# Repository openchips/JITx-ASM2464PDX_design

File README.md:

** Introduction
This is a project showing of the high speed routing capabilities within JITx. It is currently a work in progress towards an open source USB4/TBT4 to between 1 and 4 M.2 PCIe connectors based on the AsMedia ASM2464PDX chip.

The software used to write this complex design is JITx, a new and amazing code based EDA. Check out [JITx plans and **their free for open source license**.](https://hubs.la/Q02-p5-70)
Feel free to reach out to me or to their support on Discord to learn more, or plan a demo session to see how the future of PCB desgn will look like.

** To-do
WIP

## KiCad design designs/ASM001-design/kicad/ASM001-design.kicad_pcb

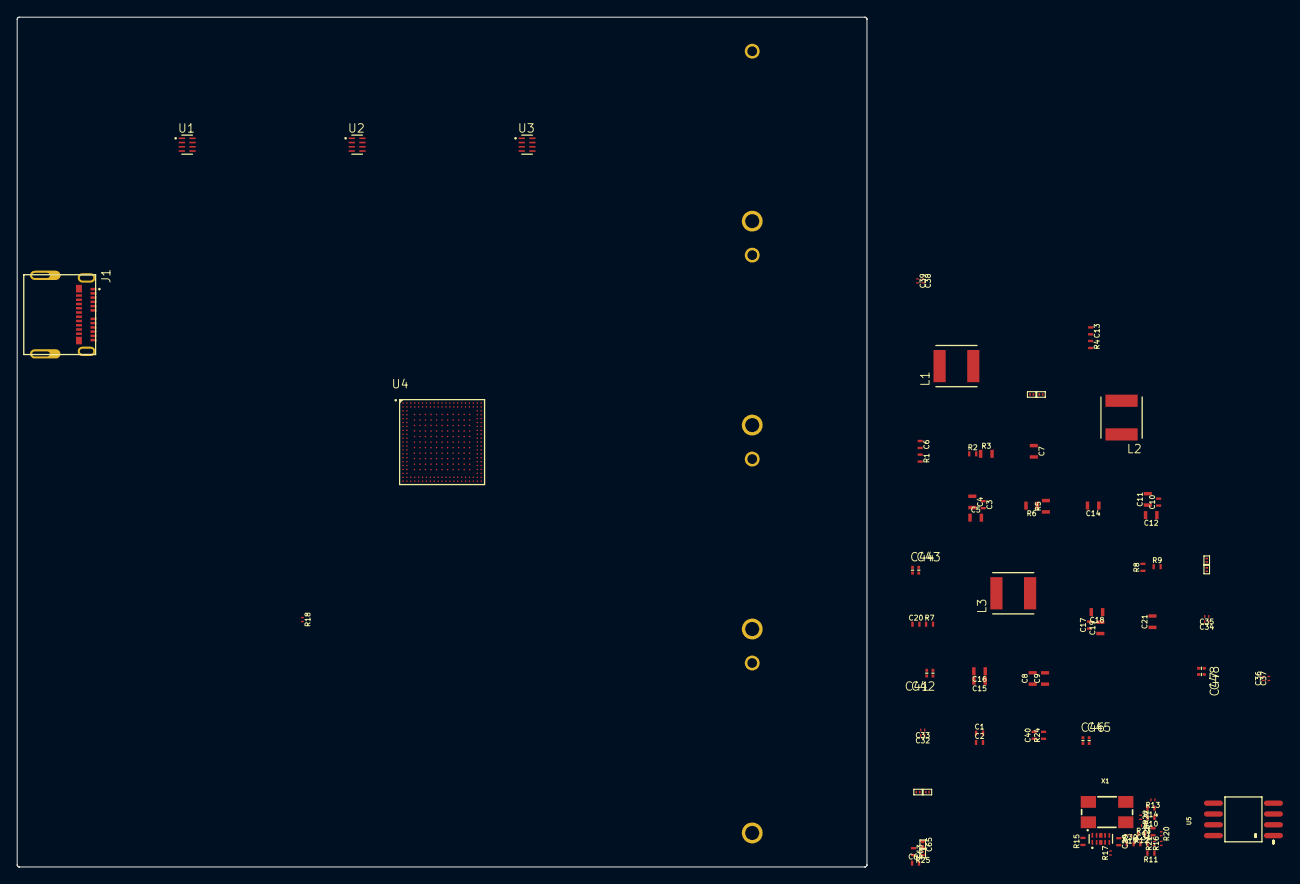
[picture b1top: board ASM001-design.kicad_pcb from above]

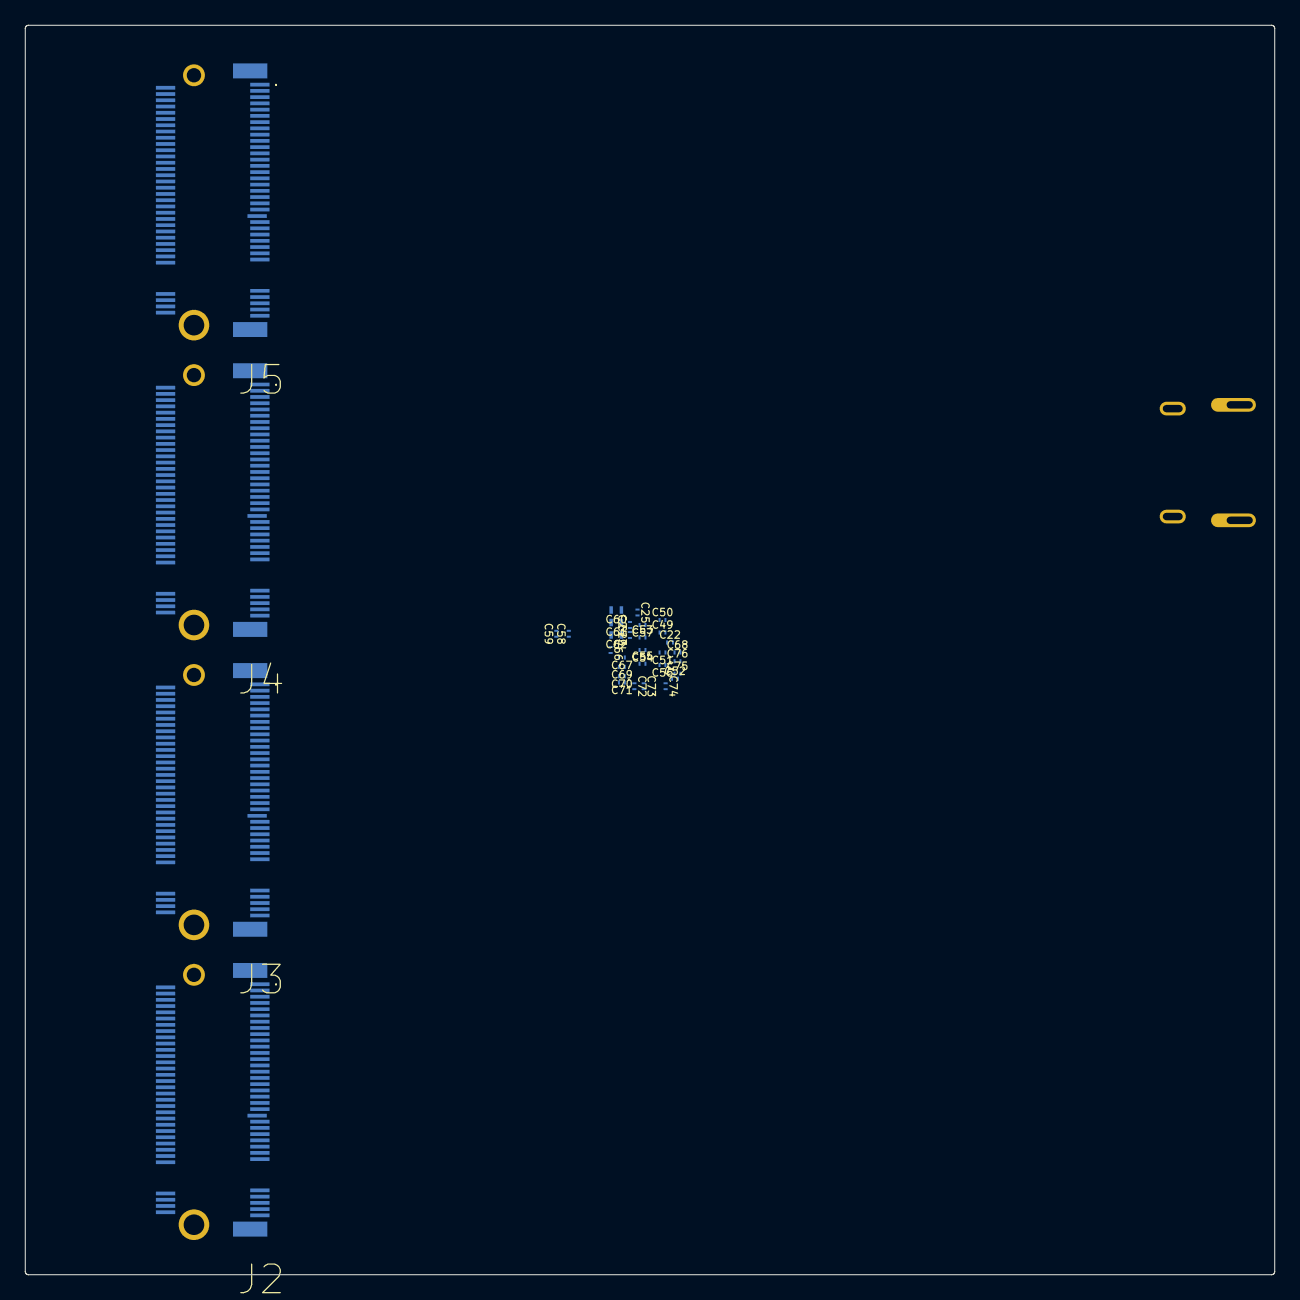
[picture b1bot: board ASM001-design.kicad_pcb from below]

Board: 6 copper layers, 100.0 x 100.0 mm, 122 parts (33 on the bottom side), 107 nets, no tracks yet.

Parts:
C1, C2: 820n; Pkg0402_12
C3: 4.7n; Pkg0402_5
C4, C5: 10u; Pkg0603_5
C6: 100n; Pkg0402_15
C7: 10p; Pkg0603_8
C8, C9: 390n; Pkg0603_10
C10: 4.7n; Pkg0402_3
C11, C12: 10u; Pkg0603_4
C13: 100n; Pkg0402_14
C14: 10p; Pkg0603_7
C15, C16: 3.3u; Pkg0603_9
C17: 4.7n; Pkg0402_2
C18, C19: 10u; Pkg0603_3
C20: 100n; Pkg0402_13
C21: 10p; Pkg0603_6
C22, C23, C24, C25: 220n; Pkg0201
C28: 10p; LP_3
C29: 1u; Pkg0402_6
C30, C31: 2.2n; Pkg0402_8
C32, C33, C36, C37: 220n; Pkg0201_5
C34, C35, C38, C39: 470n; Pkg0201_1
C40: 4.7n; Pkg0402_11
C41, C42, C43, C44, C45, C46, C47, C48: 220n; SMT_0201
C49, C50, C51, C52, C53, C54, C55, C56, C57, C58, C59: 2.2u; Pkg0201_4
C60, C61, C62: 10u; Pkg0402_20
C63, C64, C65: 10u; Pkg0402_10
C66, C67, C68, C69, C70, C71, C72, C73, C74, C75, C76: 2.2u; Pkg0201_7
J1: 2012670005; USB_TYPE_C_CONNECTOR
J2, J3, J4, J5: 1-2199230-6; Pkg_121992306
L1, L2, L3: 1.5u; MOLDED
R1: 0R; Pkg0402_19
R2: 3K09; Pkg0402_1
R3: 7K5; Pkg0603_2
R4: 0R; Pkg0402_18
R5: 10K; Pkg0603
R6: 7K32; Pkg0603_1
R7: 0R; Pkg0402_17
R8: 24K; Pkg0402
R9: 7K68; Pkg0402_4
R10, R11, R12, R15: 4K7; Pkg0402_16
R13: 100K; Pkg0201_2
R14: 12K1; Pkg0402_9
R16, R17, R18, R19, R20, R21, R22, R23: 200K; Pkg0201_6
R24: 0R; Pkg0402_7
R25: 0R; Pkg0201_3
U1, U2, U3: TPS62932DRL; SOT50P160_8N
U4: ASM2464PDX; BGA273N46P21X21_1000X1000X98
U5: W25Q32JVSSIQ; LP_1
U6: ESD224DQAR; USON_10
U7, U8, U9, U10, U11, U12, U13, U14: ESD132-B1-W0201 E6327; LP_2
X1: ABMM2-25.000MHZ-D1-T; LP

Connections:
BST: C6.1, U1.6
FB: C21.2, R8.2, R9.1, U3.8
GND: C22.2, C23.2, C24.2, C25.2, C29.2, C30.2, C31.2, C40.2, C49.2, C50.2, C51.2, C52.2, C53.2, C54.2, C55.2, C56.2, C57.2, C58.2, C59.2, C60.2, C61.2, C62.2, C63.2, C64.2, C65.2, C66.2, C67.2, C68.2, C69.2, C70.2, C71.2, C72.2, C73.2, C74.2, C75.2, C76.2, J1.A1, J1.A12, J1.B1, J1.B12, J2.3, J2.9, J2.15, J2.33, J2.39, J2.45, J2.51, J2.57, J2.71, J2.73, J3.3, J3.9, J3.15, J3.33, J3.39, J3.45, J3.51, J3.57, J3.71, J3.73, J4.3, J4.9, J4.15, J4.33, J4.39, J4.45, J4.51, J4.57, J4.71, J4.73, J5.3, J5.9, J5.15, J5.33, J5.39, J5.45, J5.51, J5.57, J5.71, J5.73, R14.2, R15.2, R16.2, R17.2, R18.2, R19.2, R20.2, R21.2, R22.2, R23.2, R24.2, U4.AA1, U4.AA2, U4.AA5, U4.AA9, U4.AA12, U4.AA14, U4.AA16, U4.AA18, U4.AA20, U4.AA21, U4.D4, U4.D5, U4.D11, U4.D17, U4.D18, U4.E4, U4.E5, U4.E17, U4.E18, U4.F4, U4.F5, U4.F8, U4.F17, U4.F18, U4.H4, U4.H8, U4.H17, U4.H18, U4.J4, U4.J5, U4.J6, U4.J11, U4.K2, U4.L1, U4.L2, U4.L4, U4.L5, U4.L9, U4.L13, U4.M20, U4.M21, U4.N1, U4.N2, U4.N4, U4.N5, U4.N9, U4.N11, U4.N13, U4.N17, U4.N18, U4.P4, U4.P5, U4.P9, U4.P11, U4.P17, U4.P18, U4.P20, U4.P21, U4.R1, U4.R2, U4.T4, U4.T5, U4.T17, U4.T18, U4.T20, U4.T21, U4.U1, U4.U2, U4.U4, U4.U5, U4.U17, U4.U18, U4.V4, U4.V5, U4.V6, U4.V8, U4.V9, U4.V11, U4.V13, U4.V14, U4.V16, U4.V17, U4.V18, U4.V20, U4.V21, U4.W1, U4.W2, U4.Y3, U4.Y5, U4.Y9, U4.Y12, U4.Y14, U4.Y16, U4.Y18, U4.Y20, U4.Y21, U5.4, U6.3, U6.8, X1.2, X1.4
GND1: C1.2, C2.2, C3.2, C4.2, C5.2, C8.2, C9.2, C10.2, C11.2, C12.2, C15.2, C16.2, C17.2, C18.2, C19.2, R3.2, R6.2, R9.2, U1.4, U2.4, U3.4
IC_SW_BST: C20.1, U3.6
IC_SW_FB: C14.2, R5.2, R6.1, U2.8
P1V9: C10.1, C11.1, C12.1, C14.1, C63.1, C64.1, C65.1, C66.1, C67.1, C68.1, C69.1, C70.1, C71.1, C72.1, C73.1, C74.1, C75.1, C76.1, L2.2, R5.1, U4.L6, U4.L16, U4.L17, U4.L18, U4.L20, U4.L21, U4.N6, U4.N16, U4.P6, U4.P16, U4.T6, U4.T16, U4.U6, U4.U11, U4.U13, U4.U14, U4.U16
P1V13: C3.1, C4.1, C5.1, C7.1, C22.1, C23.1, C24.1, C25.1, C49.1, C50.1, C51.1, C52.1, C53.1, C54.1, C55.1, C56.1, C57.1, C58.1, C59.1, C60.1, C61.1, C62.1, L1.2, R2.1, U4.D14, U4.D16, U4.E11, U4.E14, U4.E16, U4.F9, U4.F11, U4.F14, U4.F16, U4.H9, U4.H11, U4.H13, U4.H14, U4.H16, U4.J8, U4.J9, U4.J13, U4.J14, U4.J16, U4.J17, U4.J18, U4.J20, U4.J21, U4.K20, U4.K21, U4.L8, U4.L11, U4.L14, U4.N8, U4.N14, U4.P8, U4.P13, U4.P14, U4.T8, U4.T9, U4.T11, U4.T13, U4.T14, U4.U8, U4.U9
P3V3: C17.1, C18.1, C19.1, C21.1, L3.2, R8.1, R10.2, R11.2, R12.2, R13.2, R25.1, U4.D6, U4.D8, U4.D9, U4.D13, U4.E6, U4.E8, U4.E9, U4.E13, U4.F6, U4.F13, U4.H6, U5.8
RST#: C29.1, R13.1, U4.H1
R_p1: C40.1, J1.M1, J1.M2, J1.M3, J1.M4, R24.1
SHIELD: J4.MP1, J4.MP2
SHIELD1: J5.MP1, J5.MP2
SHIELD2: J2.MP1, J2.MP2
SHIELD3: J3.MP1, J3.MP2
SPI_CLK: U4.A5, U5.6
SPI_CS#: U4.A2, U5.1
SPI_DI: U4.A4, U5.5
SPI_DO: U4.A3, U5.2
SPI_IO2: R10.1, U5.3
SPI_IO3: R11.1, U5.7
SW-NODE: L1.1, R1.2, U1.5
SW-NODE1: L3.1, R7.2, U3.5
SW-NODE2: L2.1, R4.2, U2.5
SW_BST: C13.1, U2.6
SW_FB: C7.2, R2.2, R3.1, U1.8
TEST_EN: R15.1, U4.H21
UART_TX: R12.1, U4.B21
UREXT: R14.1, U4.AA3
VBUS: J1.A4, J1.A9, J1.B4, J1.B9, U4.G1
VBUS1: C1.1, C2.1, C8.1, C9.1, C15.1, C16.1, U1.3, U2.3, U3.3
VCCA33: R25.2, U4.H5
V_3V3: J5.2, J5.4, J5.12, J5.14, J5.16, J5.18, J5.70, J5.72, J5.74
V_3V3_1: J4.2, J4.4, J4.12, J4.14, J4.16, J4.18, J4.70, J4.72, J4.74
V_3V3_2: J2.2, J2.4, J2.12, J2.14, J2.16, J2.18, J2.70, J2.72, J2.74
V_3V3_3: J3.2, J3.4, J3.12, J3.14, J3.16, J3.18, J3.70, J3.72, J3.74
XI: C28.1, U4.AA4, X1.1
XO: C28.2, U4.Y4, X1.3
asm2464pdx_usb-c_cc0: C30.1, J1.A5, U4.AA6
asm2464pdx_usb-c_cc1: C31.1, J1.B5, U4.Y6
asm2464pdx_usb-c_sbu0: J1.A8, U4.K1
asm2464pdx_usb-c_sbu1: J1.B8, U4.J1
dst-ep_control_CLKREQ#: J4.52, U4.A19
dst-ep_control_CLKREQ#1: J2.52, U4.A20
dst-ep_control_CLKREQ#2: J3.52, U4.A14
dst-ep_control_PERST#: J3.50, U4.E21
dst-ep_control_PERST#1: J4.50, U4.G21
dst-ep_control_PERST#2: J5.50, U4.D21
dst-ep_control_PEWAKE#: J5.54, U4.A9
dst-ep_control_PEWAKE#1: J4.54, U4.A13
dst-ep_control_PEWAKE#2: J2.54, U4.A12
dst-ep_control_PEWAKE#3: J3.54, U4.A11
dst-ep_data_lane0_RX_P: J2.43, U4.W21
dst-ep_data_refclk_N: J5.53, U4.Y7
dst-ep_data_refclk_N1: J4.53, U4.Y8
dst-ep_data_refclk_N2: J2.53, U4.Y11
dst-ep_data_refclk_P: J5.55, U4.AA7
dst-ep_data_refclk_P1: J2.55, U4.AA11
dst-ep_data_refclk_P2: J3.55, U4.AA10
elem_elem_p1: C13.2, R4.1
elem_p1: C6.2, R1.1
elem_p2: C20.2, R7.1
esd-pair_A_P: J1.A6, J1.B6, U4.M1, U6.5, U6.6
esd-pair_B_N: J1.A7, J1.B7, U4.M2, U6.4, U6.7
src-ep_control_CLKREQ#: J5.52, U4.A15
src-ep_control_PERST#: J2.50, U4.F21
src-ep_data_lane0_RX_N: J5.41, U4.Y13
src-ep_data_lane0_RX_N1: J2.41, U4.W20
src-ep_data_lane0_RX_N2: J3.41, U4.AA19
src-ep_data_lane0_RX_N3: J4.41, U4.N20
src-ep_data_lane0_RX_P: J4.43, U4.N21
src-ep_data_lane0_RX_P1: J5.43, U4.AA13
src-ep_data_lane0_RX_P2: J3.43, U4.Y19
src-ep_data_refclk_N: J3.53, U4.Y10
src-ep_data_refclk_P: J4.55, U4.AA8
x_A_N: C35.2, U10.2
x_A_N1: C37.2, U12.2
x_A_N2: C42.2, U4.U21
x_A_N3: C48.1, U4.AA15
x_A_N4: C37.1, J1.B3, R23.1, U4.V1, U12.1
x_A_N5: C46.1, U4.R21
x_A_N6: C39.2, U14.1
x_A_N7: C39.1, J1.A10, R21.1, U4.Y1, U14.2
x_A_N8: C44.2, U4.AA17
x_A_P: C43.2, U4.Y17
x_A_P1: C38.1, J1.A11, R20.1, U4.Y2, U13.2
x_A_P2: C32.1, U7.2
x_A_P3: C34.2, U9.2
x_A_P4: C36.2, U11.2
x_A_P5: C41.2, U4.U20
x_A_P6: C47.1, U4.Y15
x_A_P7: C34.1, J1.B11, R16.1, U4.P1, U9.1
x_A_P8: C45.1, U4.R20
x_A_P9: C38.2, U13.1
x_B_N: C44.1, J3.47
x_B_N1: C33.1, U8.2
x_B_N2: C48.2, J5.47
x_B_N3: C46.2, J4.47
x_B_N4: C35.1, J1.B10, R17.1, U4.P2, U10.1
x_B_N5: C42.1, J2.47
x_B_N6: C33.2, J1.A3, R19.1, U4.T2, U8.1
x_B_P: C32.2, J1.A2, R18.1, U4.T1, U7.1
x_B_P1: C43.1, J3.49
x_B_P2: C47.2, J5.49
x_B_P3: C45.2, J4.49
x_B_P4: C36.1, J1.B2, R22.1, U4.V2, U11.1
x_B_P5: C41.1, J2.49

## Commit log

2024-11-19 Initialcommit
    Current state of the work in progress on this project
2024-11-19 Cleanup
2024-11-19 Updated ASM2464PDX component to more modern JSL syntax. jitx.exe crashes with unknown code
2024-11-19 Update files
2024-12-07 Update device definitions and some tests
2024-12-08 Update USB4 supports, WIP
2024-12-10 Attempt to add usb-c support to the USB4 connector
2024-12-11 Updated USB4 connector to finally render
2024-12-11 Add .viw to gitignore
2024-12-11 Add PCIe constraints and iterate over the 2 USB channels. TODO: strange error about unroutable pin
2024-12-11 Cleaner way of iterating over USB-C lanes
2024-12-12 Semi-working, rendering at least
2024-12-12 Bard files
2024-12-16 Updates to the USB4 connector
    Thanks @callendorph for your feedback and help, it has been super valuable.
2025-01-11 Properly name and version the project. Small changes to update to latest jsl
2025-01-11 Fill in some details from the USB4 cable and system guide
2025-01-11 Some toying around to see if I can figure out why it's not connected up internally
2025-01-11 require usb-data : dual-pair from self
2025-01-11 Trial and error
2025-01-11 Add generic Molex USB-C and try to connect up the USB4 constraints using the usb-c support
    It renders, but it doesn't connect up properly due to components\Generic\USBTypeC.stanza:277
2025-01-11 Add in the lane-pair suppport by Carl, maybe useful?
2025-01-11 Add 'require usb_c_inst:usb_c from self' to force error sooner.
2025-01-12 Changed to a flat component with all the constraints in the main design
2025-01-14 Some cleanup, added power supplies, starting to hook up components
2025-01-14 Large update to design, started to split components into separate pcb-modules
2025-01-14 Change PCIE-V3 back to PCIE-V4
2025-01-15 More big updates
2025-01-16 More design updates according to reference design.
2025-01-17 Start placement in code
2025-01-18 Add GND and VDD planes
2025-01-19 Cleaned up power supplies. Has issues with the PCIe 4x1 require
2025-01-19 Random testing
2025-01-20 Small bugfixes as per review by @bhusang
2025-01-22 WIP adding decoupling caps and some small changes
2025-01-24 Sloppy mix of older than jsl update esd diode changes and an attempt to implement the new PCIe supports
2025-01-24 Fixed some user error, made start at high speed diode pool
2025-01-25 No ratsnetsting+ 8 topo errors
